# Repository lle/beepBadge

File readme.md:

# BEEP BADGE
This project is inspired from a mix of concepts between an old product I was working on at my ex-job, a badge I wanted to make for a rave, the animal crossing tune creator. 
Result: a weird beeper badge XD

## Instruction
Go meet people at the con. Plug your badges together. The first person on the left presses "PLAY". The badge will start playing their 
tunes from left to right. Go make the coolest musical sequence!

## How to Program
Use an Atmel USB-ISP (USBASP) to flash the firmware. There is a programming connector at the top left of the badge labeled "Prog Port". Note the positive (+), negative (-) and reset (rst) label around the connector. Use it to match with the pinout of the USB-ISP. 
I used VScode+platformio to program and compile the firmware

## Acknowledgment
I would like to thank Angel for their help in beta-testing the badge as they are much 
more musically inclined than 
I will ever be ^.^

Parts of the design from the Northsec Pegasis badge and the "Hello my name is" badge was used to rush the design of this badge.

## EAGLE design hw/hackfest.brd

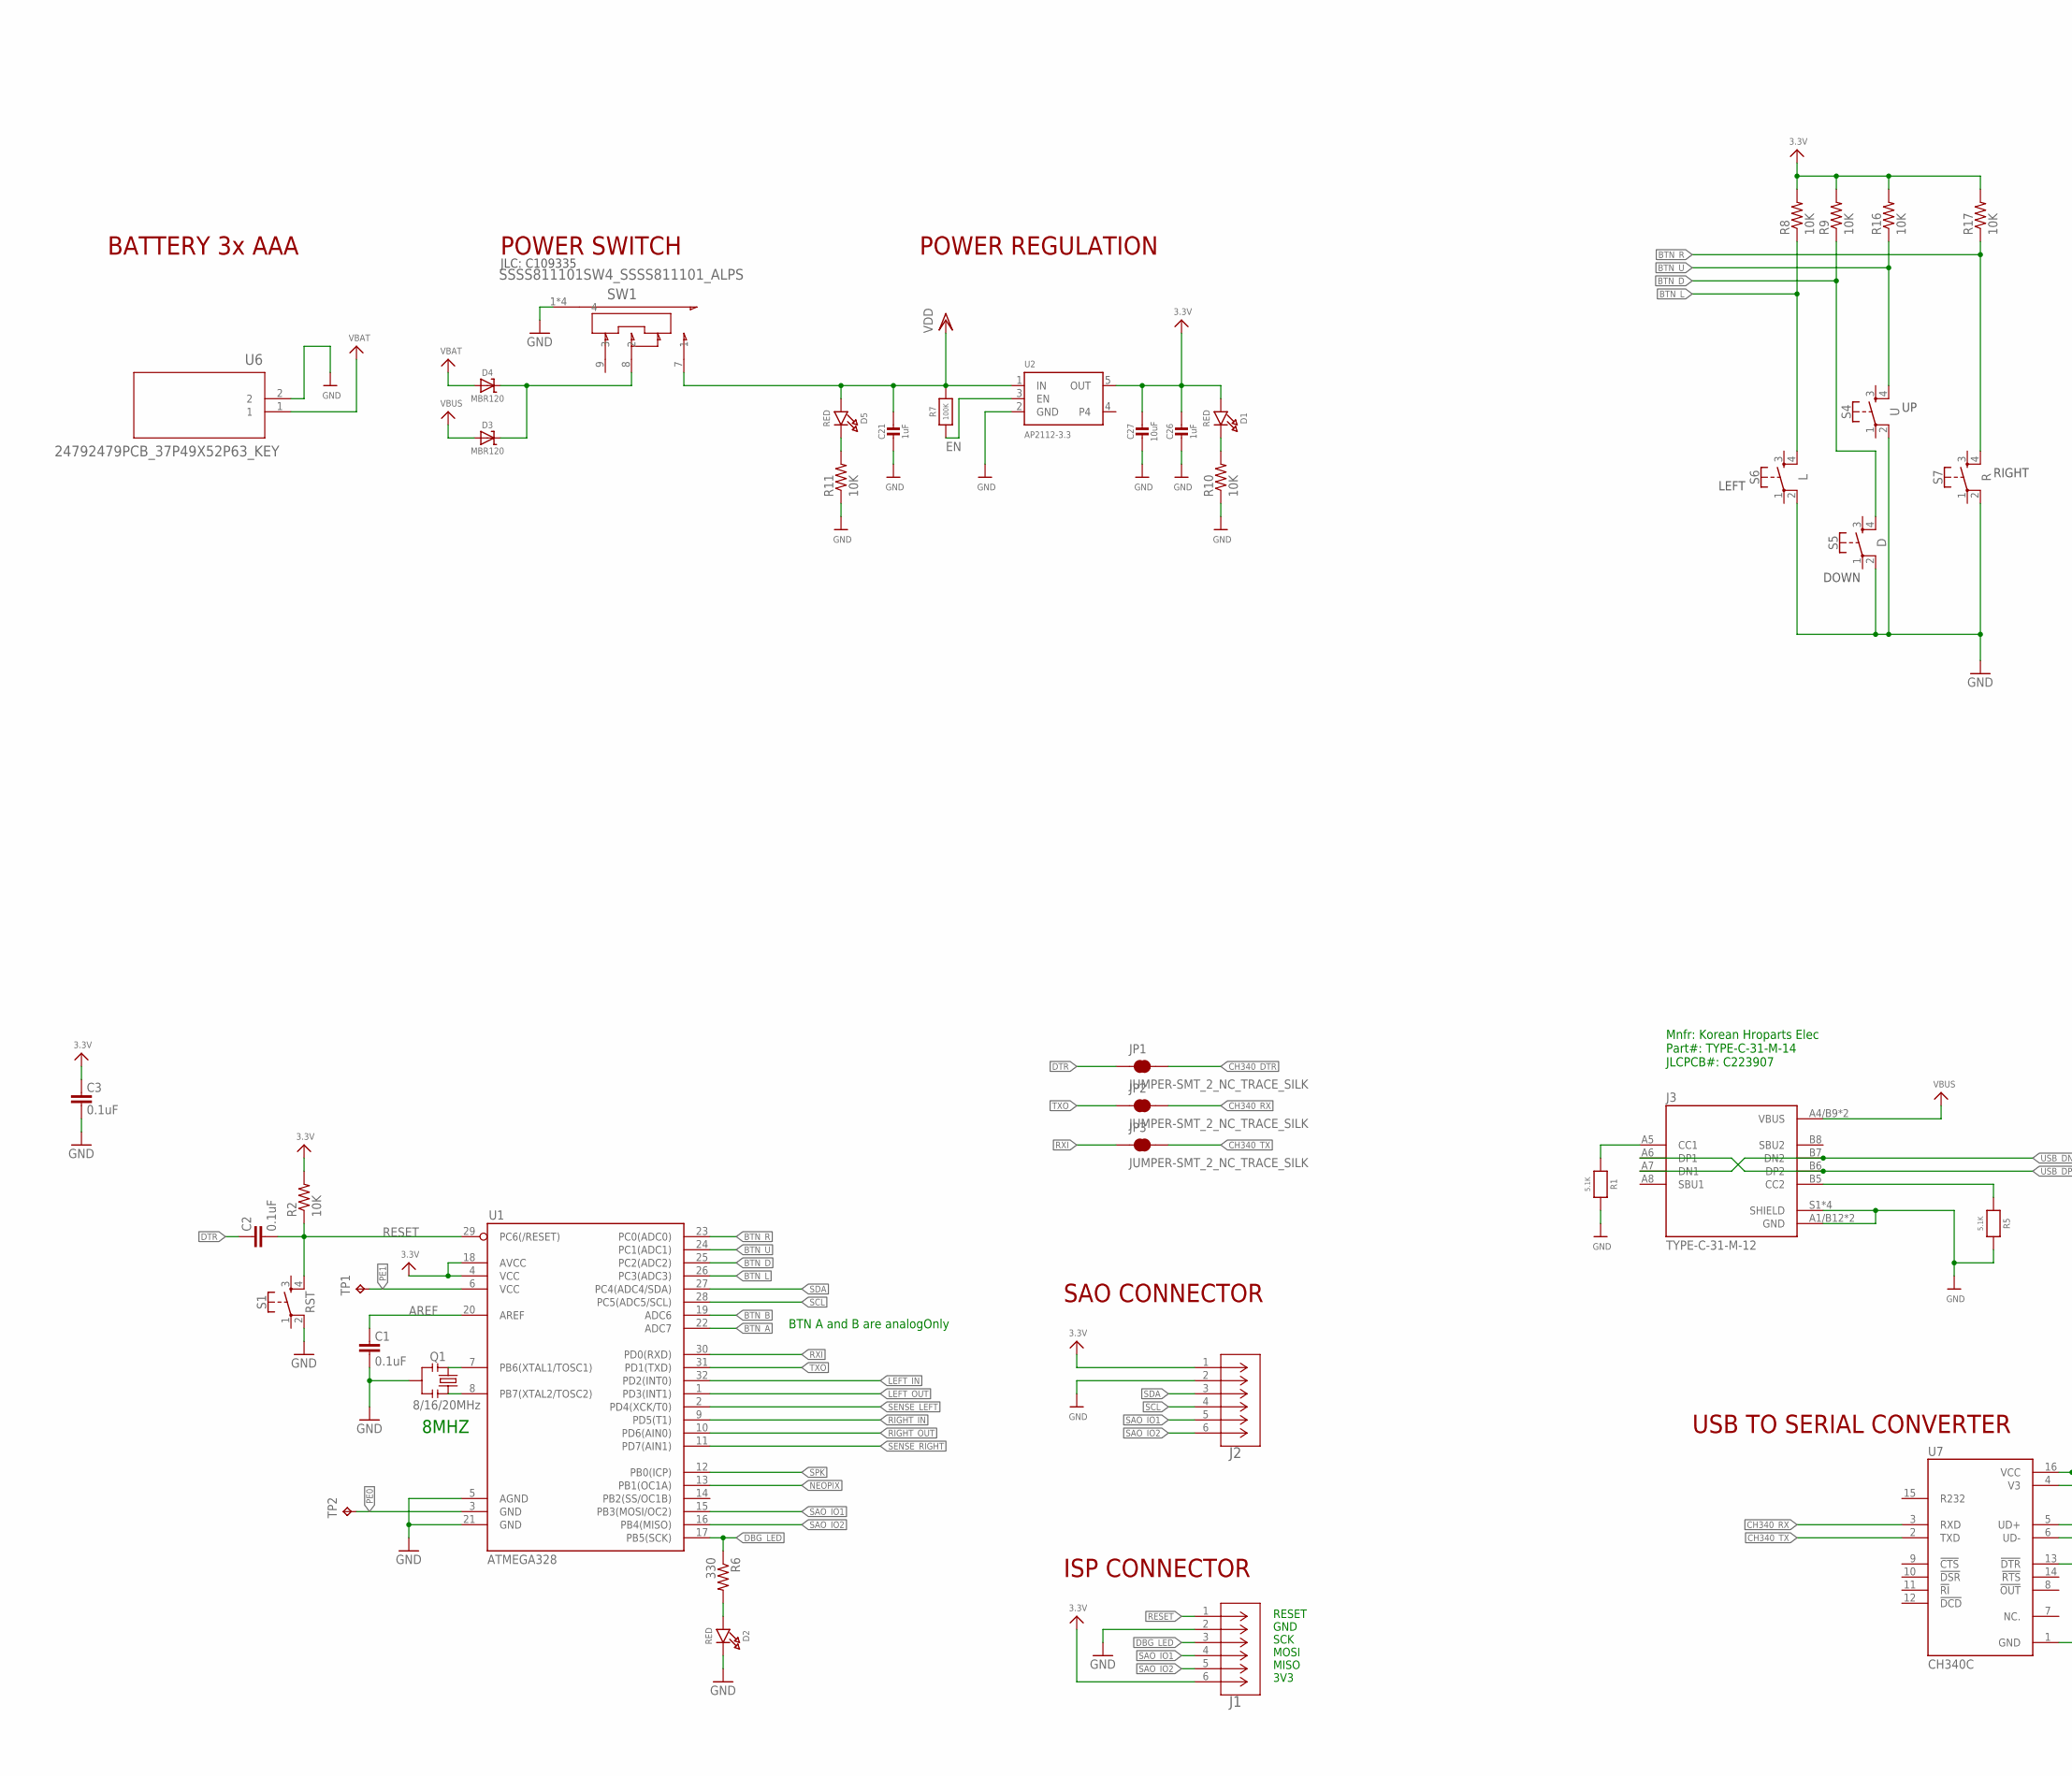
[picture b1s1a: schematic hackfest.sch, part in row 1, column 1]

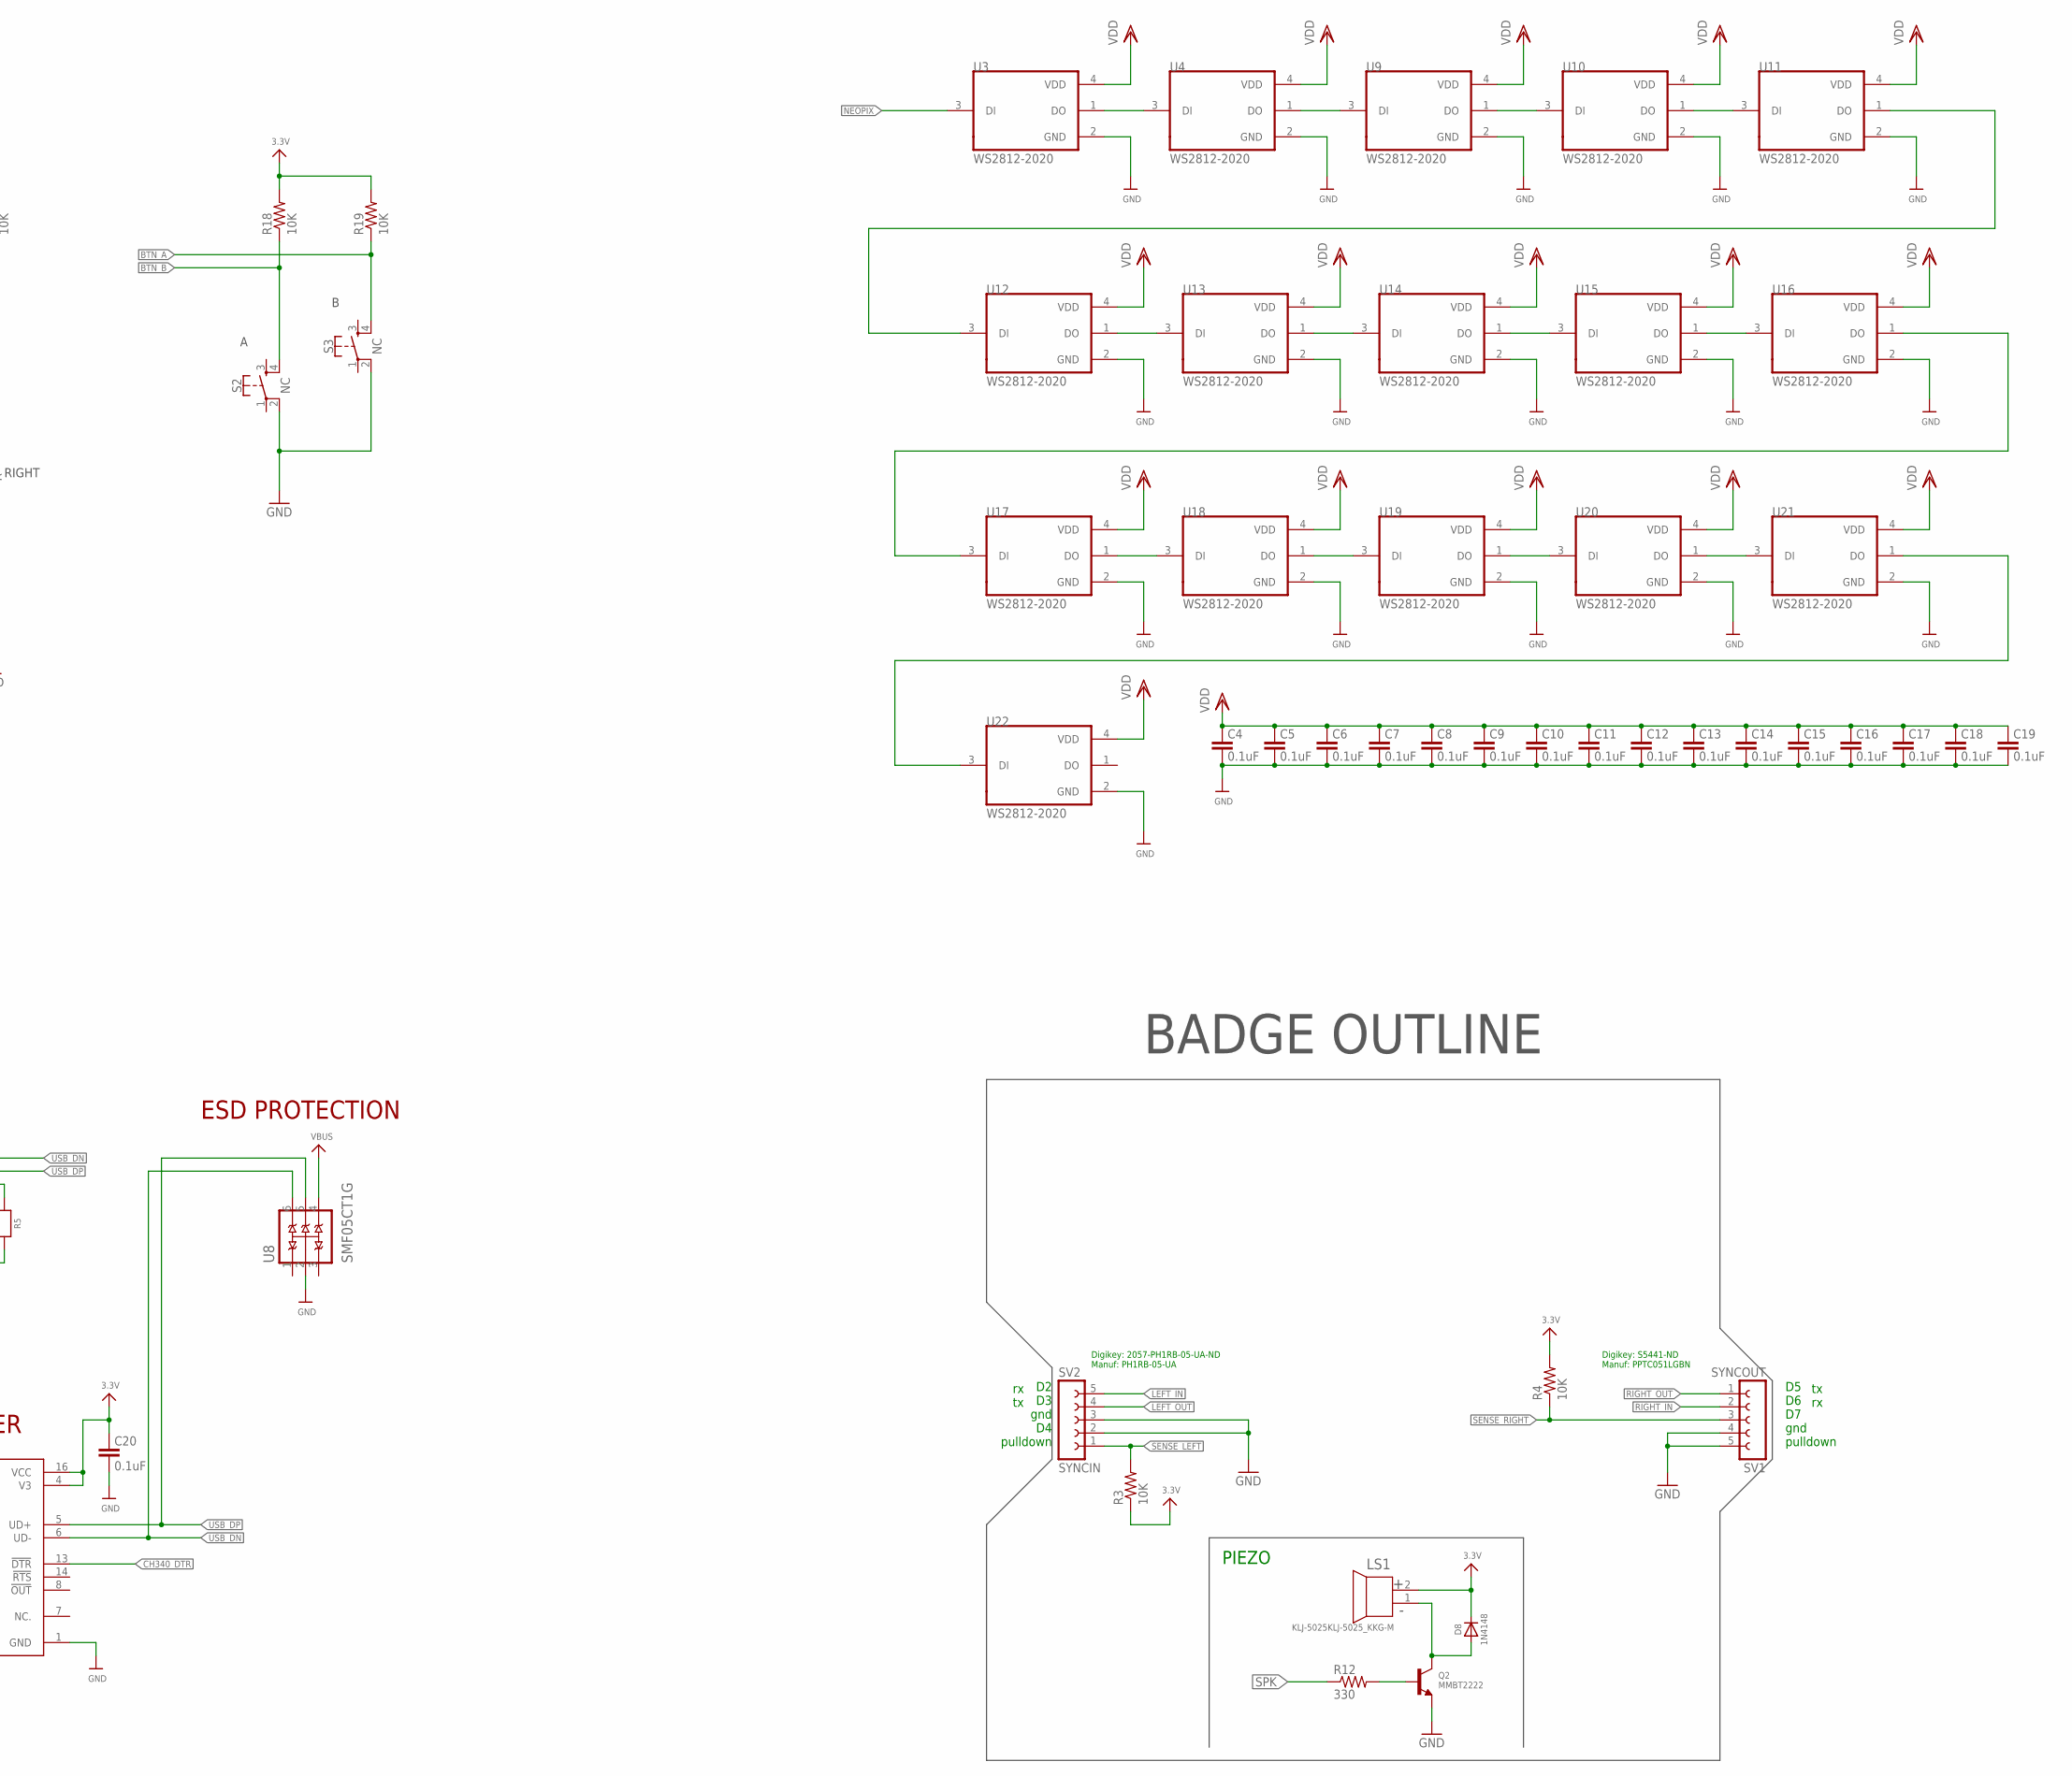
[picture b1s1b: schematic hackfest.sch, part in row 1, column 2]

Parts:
C1, C2, C3, C4, C5, C6, C7, C8, C9, C10, C11, C12, C13, C14, C15, C16, C17, C18, C19, C20: 0.1uF; 0603-CAP
C21, C26: 1uF; 0603-NO@1
C27: 10uF; 0805-NO
D1, D2, D5: RED; CHIPLED_0805_NOOUTLINE
D3, D4: MBR120; SOD-123
D8: 1N4148; SOD-323
J1, J2: SSW-103-22-F-D-VS-K-TRCON3_SSW-D-DUMZ_HDR_SAI; CON3_SSW-D-DUMZ_HDR_SAI
J3: TYPE-C-31-M-12; HRO_TYPE-C-31-M-12
JP1, JP2, JP3: JUMPER-SMT_2_NC_TRACE_SILK; SMT-JUMPER_2_NC_TRACE_SILK
LS1: KLJ-5025KLJ-5025_KKG-M; KLJ-5025_KKG-M
Q1: 8/16/20MHz; RESONATOR-SMD-1:1
Q2: MMBT2222; SOT23-WIDE
R1, R5: 5.1K; 0603-NO
R2, R3, R4, R8, R9, R10, R11, R16, R17, R18, R19: 10K; 0603-RES
R6, R12: 330; 0603-RES
R7: 100K; 0603-NO
S1: RST; TACTILE_SWITCH_SMD_5.2MM
S2, S3: NC; TACTILE_SWITCH_SMD_5.2MM
S4: U; TACTILE_SWITCH_SMD_5.2MM
S5: D; TACTILE_SWITCH_SMD_5.2MM
S6: L; TACTILE_SWITCH_SMD_5.2MM
S7: R; TACTILE_SWITCH_SMD_5.2MM
SV1: SYNCOUT; FE05W
SV2: SYNCIN; FE05W
SW1: SSSS811101SW4_SSSS811101_ALPS; SW4_SSSS811101_ALPS
TP1, TP2: TPB1,27; B1,27
U1: ATMEGA328; TQFP32-08
U2: AP2112-3.3; SOT23-5
U3, U4, U9, U10, U11, U12, U13, U14, U15, U16, U17, U18, U19, U20, U21, U22: WS2812-2020; LED_WS2812-2020
U6: 24792479PCB_37P49X52P63_KEY; 2479PCB_37P49X52P63_KEY
U7: CH340C; SOIC127P600X180-16N
U8: SMF05CT1G; SOT65P210X110-6N

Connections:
3.3V: C3.2, C20.2, C26.1, C27.1, D1.A, D8.C, J1.6, J2.1, LS1.2, R2.2, R3.1, R4.2, R8.2, R9.2, R16.2, R17.2, R18.2, R19.2, U1.4 (VCC), U1.18 (AVCC), U2.5 (OUT), U7.4 (V3), U7.16 (VCC)
AREF: C1.2, U1.20 (AREF)
BTN_A: R19.1, S3.4, U1.22 (ADC7)
BTN_B: R18.1, S2.4, U1.19 (ADC6)
BTN_D: R9.1, S5.4, U1.25 (PC2(ADC2))
BTN_L: R8.1, S6.4, U1.26 (PC3(ADC3))
BTN_R: R17.1, S7.4, U1.23 (PC0(ADC0))
BTN_U: R16.1, S4.4, U1.24 (PC1(ADC1))
CH340_DTR: JP1.2, U7.13 (!DTR)
CH340_RX: JP2.2, U7.3 (RXD)
CH340_TX: JP3.2, U7.2 (TXD)
DBG_LED: J1.3, R6.1, U1.17 (PB5(SCK))
DTR: C2.2, JP1.1
EN: R7.1, U2.3 (EN)
GND: C1.1, C3.1, C4.1, C5.1, C6.1, C7.1, C8.1, C9.1, C10.1, C11.1, C12.1, C13.1, C14.1, C15.1, C16.1, C17.1, C18.1, C19.1, C20.1, C21.2, C26.2, C27.2, D2.C, J1.2, J2.2, J3.A1/B12 (GND), J3.B1/A12 (GND), J3.S1 (SHIELD), J3.S2 (SHIELD), J3.S3 (SHIELD), J3.S4 (SHIELD), Q1.2, Q2.2 (E), R1.2, R5.2, R10.1, R11.1, S1.2, S2.2, S3.2, S4.2, S5.2, S6.2, S7.2, SV1.4, SV1.5, SV2.2, SV2.3, SW1.1 (4), SW1.2 (4), SW1.3 (4), SW1.4, U1.5 (AGND), U1.21 (GND), U2.2 (GND), U3.2 (GND), U4.2 (GND), U6.2, U7.1 (GND), U8.2 (A), U9.2 (GND), U10.2 (GND), U11.2 (GND), U12.2 (GND), U13.2 (GND), U14.2 (GND), U15.2 (GND), U16.2 (GND), U17.2 (GND), U18.2 (GND), U19.2 (GND), U20.2 (GND), U21.2 (GND), U22.2 (GND)
LEFT_IN: SV2.5, U1.32 (PD2(INT0))
LEFT_OUT: SV2.4, U1.1 (PD3(INT1))
unnamed: Q1.3, U1.8 (PB7(XTAL2/TOSC2))
unnamed: Q1.1, U1.7 (PB6(XTAL1/TOSC1))
unnamed: U4.1 (DO), U9.3 (DI)
unnamed: U9.1 (DO), U10.3 (DI)
unnamed: U3.1 (DO), U4.3 (DI)
unnamed: U10.1 (DO), U11.3 (DI)
unnamed: D2.A, R6.2
unnamed: U11.1 (DO), U12.3 (DI)
unnamed: U12.1 (DO), U13.3 (DI)
unnamed: U13.1 (DO), U14.3 (DI)
unnamed: U14.1 (DO), U15.3 (DI)
unnamed: U15.1 (DO), U16.3 (DI)
unnamed: U16.1 (DO), U17.3 (DI)
unnamed: U17.1 (DO), U18.3 (DI)
unnamed: U18.1 (DO), U19.3 (DI)
unnamed: U19.1 (DO), U20.3 (DI)
unnamed: U20.1 (DO), U21.3 (DI)
unnamed: U21.1 (DO), U22.3 (DI)
unnamed: D8.A, LS1.1, Q2.3 (C)
unnamed: Q2.1 (B), R12.2
unnamed: J3.B5 (CC2), R5.1
unnamed: J3.A5 (CC1), R1.1
unnamed: D3.C, D4.C, SW1.8 (2)
unnamed: D5.C, R11.2
unnamed: D1.C, R10.2
NEOPIX: U1.13 (PB1(OC1A)), U3.3 (DI)
PE0: TP2.TP, U1.3 (GND)
PE1: TP1.TP, U1.6 (VCC)
RESET: C2.1, J1.1, R2.1, S1.4, U1.29 (PC6(/RESET))
RIGHT_IN: SV1.2, U1.9 (PD5(T1))
RIGHT_OUT: SV1.1, U1.10 (PD6(AIN0))
RXI: JP3.1, U1.30 (PD0(RXD))
SAO_IO1: J1.4, J2.5, U1.15 (PB3(MOSI/OC2))
SAO_IO2: J1.5, J2.6, U1.16 (PB4(MISO))
SCL: J2.4, U1.28 (PC5(ADC5/SCL))
SDA: J2.3, U1.27 (PC4(ADC4/SDA))
SENSE_LEFT: R3.2, SV2.1, U1.2 (PD4(XCK/T0))
SENSE_RIGHT: R4.1, SV1.3, U1.11 (PD7(AIN1))
SPK: R12.1, U1.12 (PB0(ICP))
TXO: JP2.1, U1.31 (PD1(TXD))
USB_DN: J3.A7 (DN1), J3.B7 (DN2), U7.6 (UD-), U8.6 (C5)
USB_DP: J3.A6 (DP1), J3.B6 (DP2), U7.5 (UD+), U8.5 (C4)
VBAT: D4.A, U6.1
VBUS: D3.A, J3.A4/B9 (VBUS), J3.B4/A9 (VBUS), U8.4 (C3)
VDD: C4.2, C5.2, C6.2, C7.2, C8.2, C9.2, C10.2, C11.2, C12.2, C13.2, C14.2, C15.2, C16.2, C17.2, C18.2, C19.2, C21.1, D5.A, R7.2, SW1.7 (1), U2.1 (IN), U3.4 (VDD), U4.4 (VDD), U9.4 (VDD), U10.4 (VDD), U11.4 (VDD), U12.4 (VDD), U13.4 (VDD), U14.4 (VDD), U15.4 (VDD), U16.4 (VDD), U17.4 (VDD), U18.4 (VDD), U19.4 (VDD), U20.4 (VDD), U21.4 (VDD), U22.4 (VDD)

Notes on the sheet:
POWER REGULATION
BATTERY 3x AAA
DOWN
LEFT
RIGHT
USB TO SERIAL CONVERTER
ESD PROTECTION
BADGE OUTLINE
Mnfr: Korean Hroparts Elec Part#: TYPE-C-31-M-14 JLCPCB#: C223907
SAO CONNECTOR
RESET GND SCK MOSI MISO 3V3
ISP CONNECTOR
Digikey: S5441-ND Manuf: PPTC051LGBN
Digikey: 2057-PH1RB-05-UA-ND Manuf: PH1RB-05-UA
8MHZ
D2 D3 gnd D4 pulldown
D5 D6 D7 gnd pulldown
rx tx
tx rx
BTN A and B are analogOnly
PIEZO
JLC: C109335
POWER SWITCH

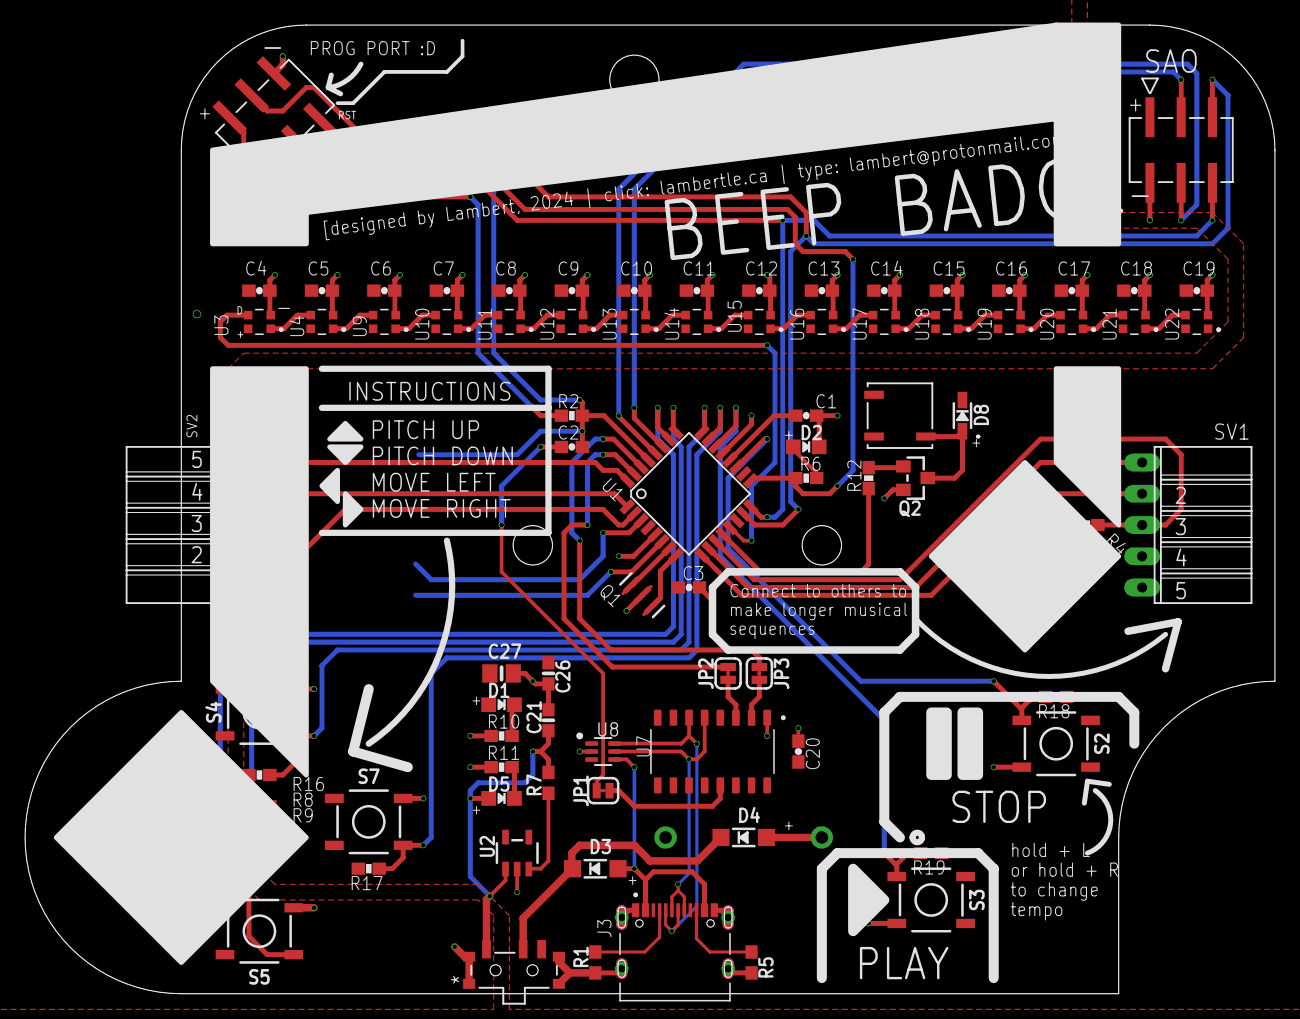
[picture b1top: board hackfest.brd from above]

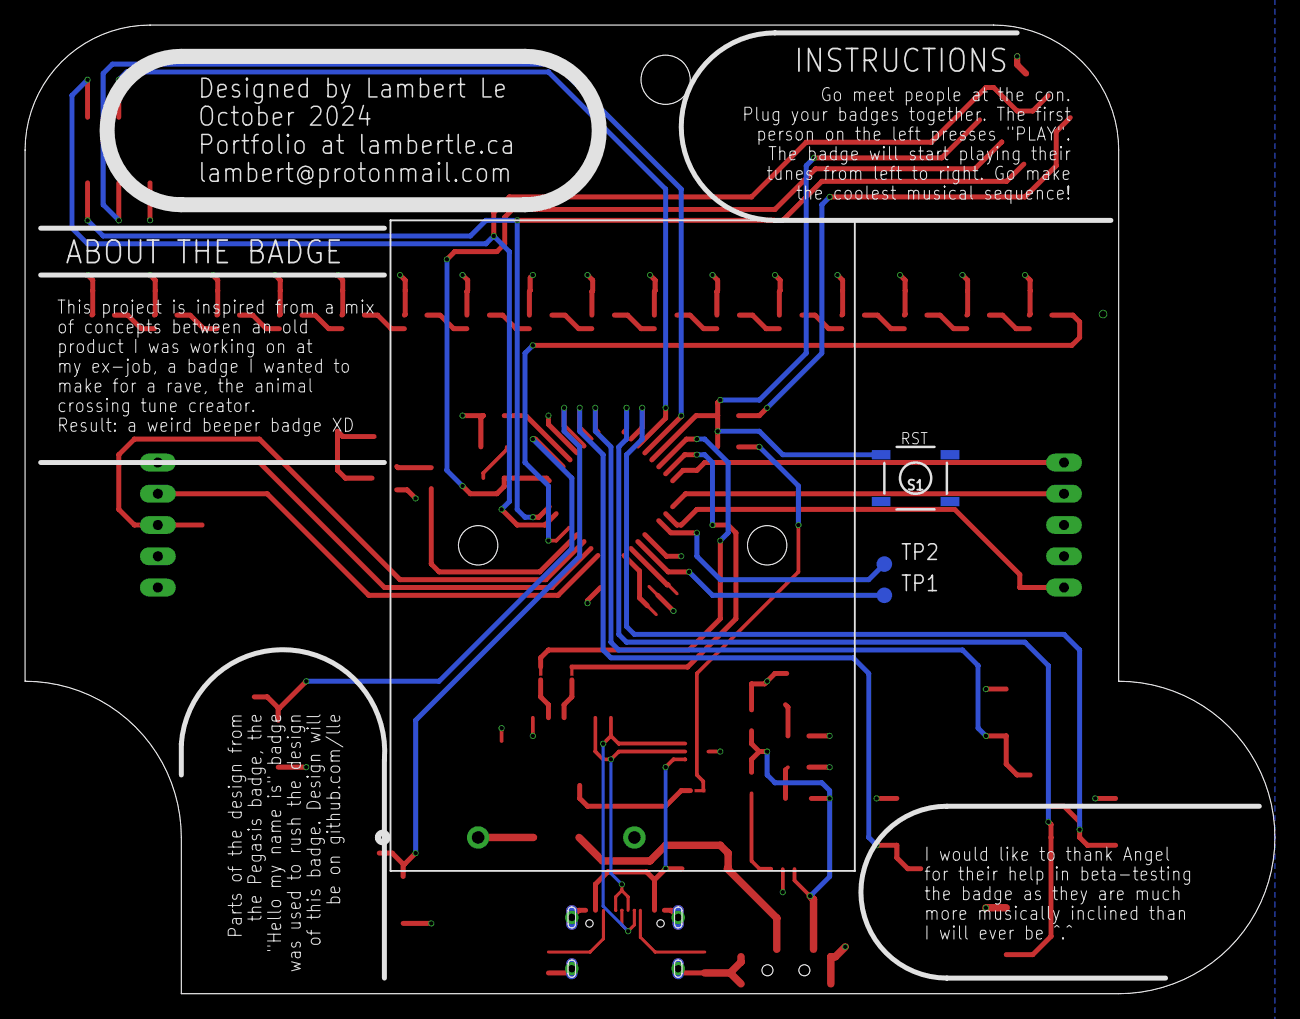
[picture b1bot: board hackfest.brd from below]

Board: 2 copper layers, 101.6 x 78.7 mm, 87 parts (4 on the bottom side), 62 nets.

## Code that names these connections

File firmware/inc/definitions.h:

#ifndef DEFINITIONS

#include "Arduino.h"
#include <Adafruit_NeoPixel.h>

// -------------- GPIO CONFIG --------------
#define BTN_U A1
#define BTN_L A3
#define BTN_R A0
#define BTN_D A2
#define BTN_A A7
#define BTN_B A6
#define DEBUG_LED 13
#define LEFT_IN 2
#define LEFT_OUT 3
#define LEFT_SENSE 4
#define RIGHT_IN 5
#define RIGHT_OUT 6
#define RIGHT_SENSE 7

// -------------- NEOPIXEL COLORS --------------
#define NEOPIX_PIN 9
#define NUMPIX 16

// -------------- NOTES TONES --------------
#define BUZZER_PIN 8    // change this to whichever pin you want to use
#define MIN_TONE 0
#define MAX_TONE 16

// Timestamps Schedulers
#define CURSOR_BLK_DELAY 50

#endif

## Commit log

2024-10-11 Release for Hackfest
    Firmware and hardware are now open source for all to play with
2024-10-11 create placeholder readme
2024-10-13 corrected reported bug in the uart output

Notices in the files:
parts and their libraries:
microbuilder: This work is placed in the public domain, and may be freely used for commercial and non-commercial work with the following conditions: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
SparkFun-Switches: Licensing: Creative Commons ShareAlike 4.0 International - https://creativecommons.org/licenses/by-sa/4.0
